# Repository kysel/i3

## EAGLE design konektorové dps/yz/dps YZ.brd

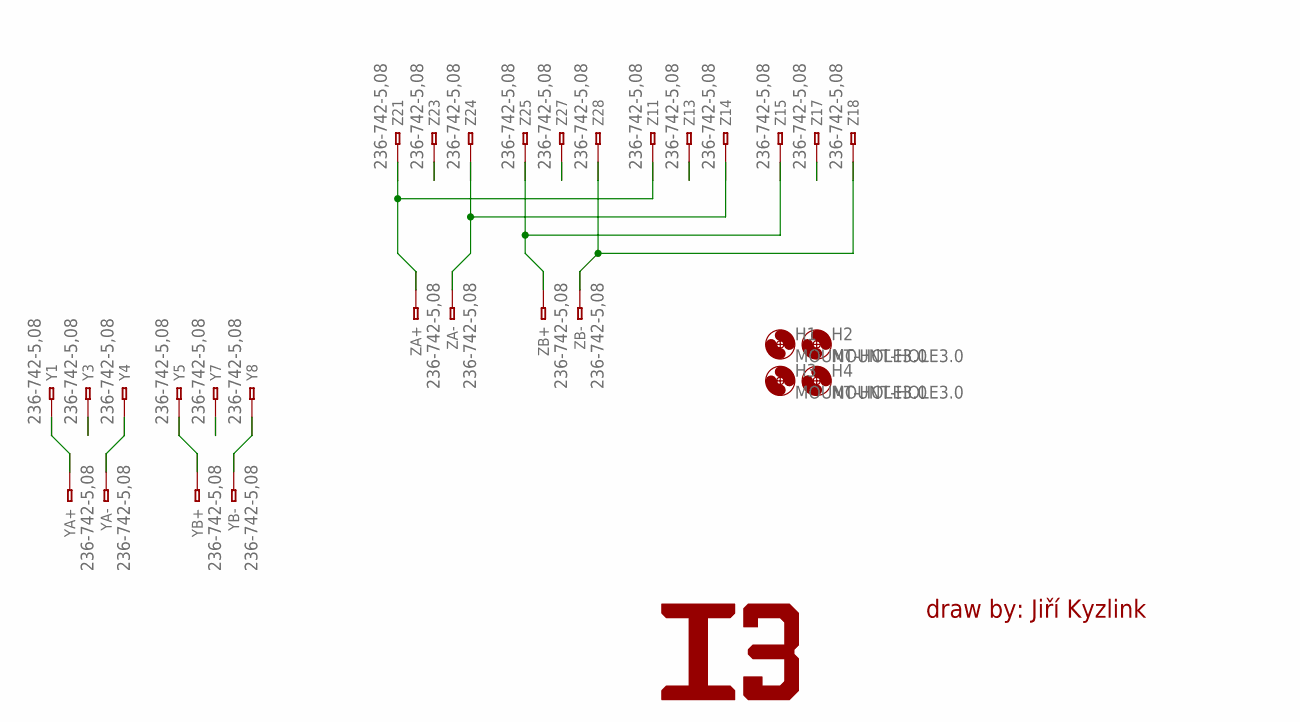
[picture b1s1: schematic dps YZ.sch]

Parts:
H1, H2, H3, H4: MOUNT-HOLE3.0; 3,0
Y1, Y3, Y4, Y5, Y7, Y8: 236-742-5,08; 236-4XX
YA+: 236-742-5,08; 236-4XX
YA-: 236-742-5,08; 236-4XX
YB+: 236-742-5,08; 236-4XX
YB-: 236-742-5,08; 236-4XX
Z11, Z13, Z14, Z15, Z17, Z18, Z21, Z23, Z24, Z25, Z27, Z28: 236-742-5,08; 236-4XX
ZA+: 236-742-5,08; 236-4XX
ZA-: 236-742-5,08; 236-4XX
ZB+: 236-742-5,08; 236-4XX
ZB-: 236-742-5,08; 236-4XX

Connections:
unnamed: Z23.1@1 (A1), Z23.1@2 (B1)
unnamed: Y3.1@1 (A1), Y3.1@2 (B1)
unnamed: Y7.1@1 (A1), Y7.1@2 (B1)
unnamed: Y8.1@1 (A1), Y8.1@2 (B1), YB-.1@1 (A1), YB-.1@2 (B1)
unnamed: Z27.1@1 (A1), Z27.1@2 (B1)
unnamed: Z17.1@1 (A1), Z17.1@2 (B1)
unnamed: Y5.1@1 (A1), Y5.1@2 (B1), YB+.1@1 (A1), YB+.1@2 (B1)
unnamed: Z13.1@1 (A1), Z13.1@2 (B1)
unnamed: Z11.1@1 (A1), Z11.1@2 (B1), Z21.1@1 (A1), Z21.1@2 (B1), ZA+.1@1 (A1), ZA+.1@2 (B1)
unnamed: Z14.1@1 (A1), Z14.1@2 (B1), Z24.1@1 (A1), Z24.1@2 (B1), ZA-.1@1 (A1), ZA-.1@2 (B1)
unnamed: Z15.1@1 (A1), Z15.1@2 (B1), Z25.1@1 (A1), Z25.1@2 (B1), ZB+.1@1 (A1), ZB+.1@2 (B1)
unnamed: Z18.1@1 (A1), Z18.1@2 (B1), Z28.1@1 (A1), Z28.1@2 (B1), ZB-.1@1 (A1), ZB-.1@2 (B1)
unnamed: Y4.1@1 (A1), Y4.1@2 (B1), YA-.1@1 (A1), YA-.1@2 (B1)
unnamed: Y1.1@1 (A1), Y1.1@2 (B1), YA+.1@1 (A1), YA+.1@2 (B1)

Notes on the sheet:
draw by: Jiří Kyzlink

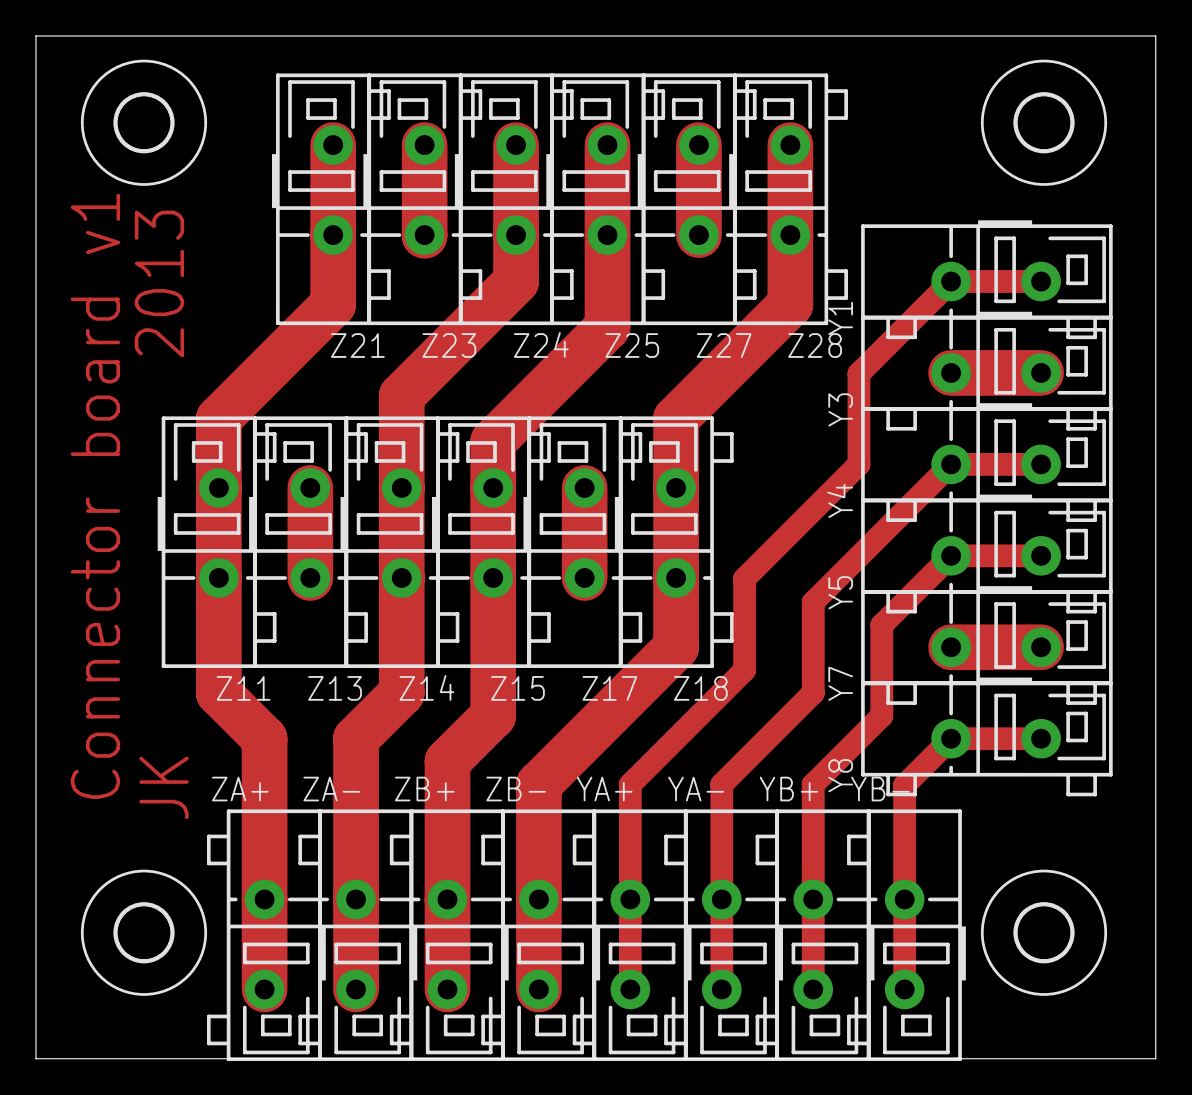
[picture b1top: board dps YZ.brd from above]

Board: 2 copper layers, 62.2 x 56.8 mm, 30 parts (0 on the bottom side), 14 nets.

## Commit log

2013-06-18 1. commit :D
2013-06-18 move dokumetace
